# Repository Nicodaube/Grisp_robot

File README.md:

# GRiSP2 Robot

## Introduction

This project is an extension of the master thesis made by Francois Goens and Cédric Ponsard (link [here](https://github.com/FrancoisGgg/balancing_robot) (2023-2024)). It is done in the context of a new master thesis by Nicolas Daube and Thomas Vanbever (2024-2025). Both of these master thesis where done under the supervision of Prof. Peter Van Roy at UCLouvain. The goal of this project is to use [GRISP2 boards](https://github.com/grisp/grisp) (designed and comercialised by [Peer Stritzinger GMBH.](https://stritzinger.com/)) and the [Hera](https://github.com/Nicodaube/hera) framework to create a robot capable of standing upright (last master thesis) and to know its own position in an assembly of rooms (current project). The robot, and its associated sensors, need to know at all time the position of the robot in the system of rooms. Each sensor knows all the data sent by each sensors and by the robot. An other goal of this project is thus to allow each sensor to compute the position of the robot (using a Kalman Filter) at a reasonable rate. This implies that the filter must evolve over time, using the data given by the right sensors at the right time.

The project is done using Erlang OTP (current version 27.2.4). If you want more informations about the, project, visit our the [Wiki](https://github.com/Nicodaube/Grisp_robot/wiki) section of this repository.

## Organisation

This repository is organised in several subdirectories :

* **Hardware_robot** : contains all the necessary files to build the robot. In `Hardware_robot/printing_files` you will find all the files for the prints in 3D and the laser cuts.
* **Hardware_sensor** : Contains all the necessary files to build the sensors and their supports.
* **Laptop_controller** : contains all the code concerning the python server and controller for the robot. Note that its use is mandatory to have a fully functional system.
* **LilyGo_software** : contains all the code for the two LilyGO used in this project. They are used for communication between the robot and the controller.
* **Wiki_image** : just a directory containing all the wiki and README images.
* **balancing_robot** : contains all the code for the auto-stabilized robot.
* **electronics**: contains the files concerning the custom PCB designed for the robot.
* **sensor**: contains all the erlang code for the implementation of the sonar sensors.

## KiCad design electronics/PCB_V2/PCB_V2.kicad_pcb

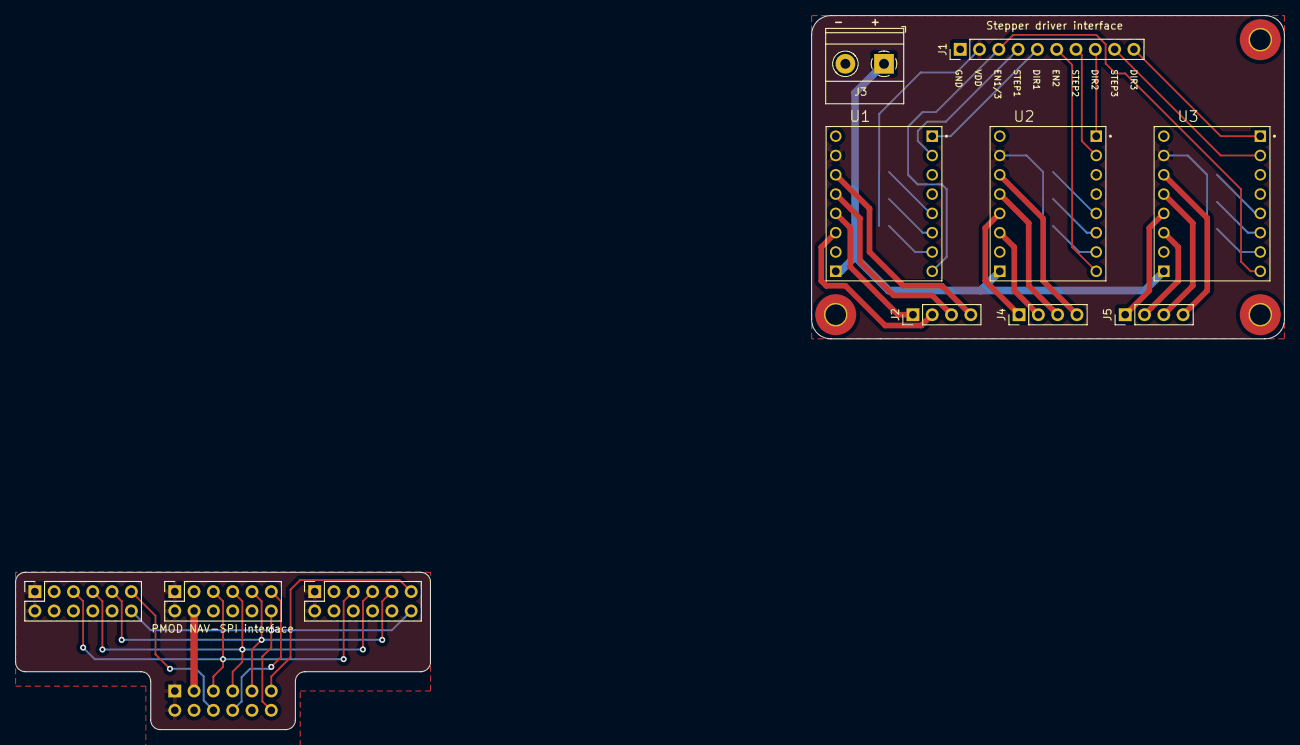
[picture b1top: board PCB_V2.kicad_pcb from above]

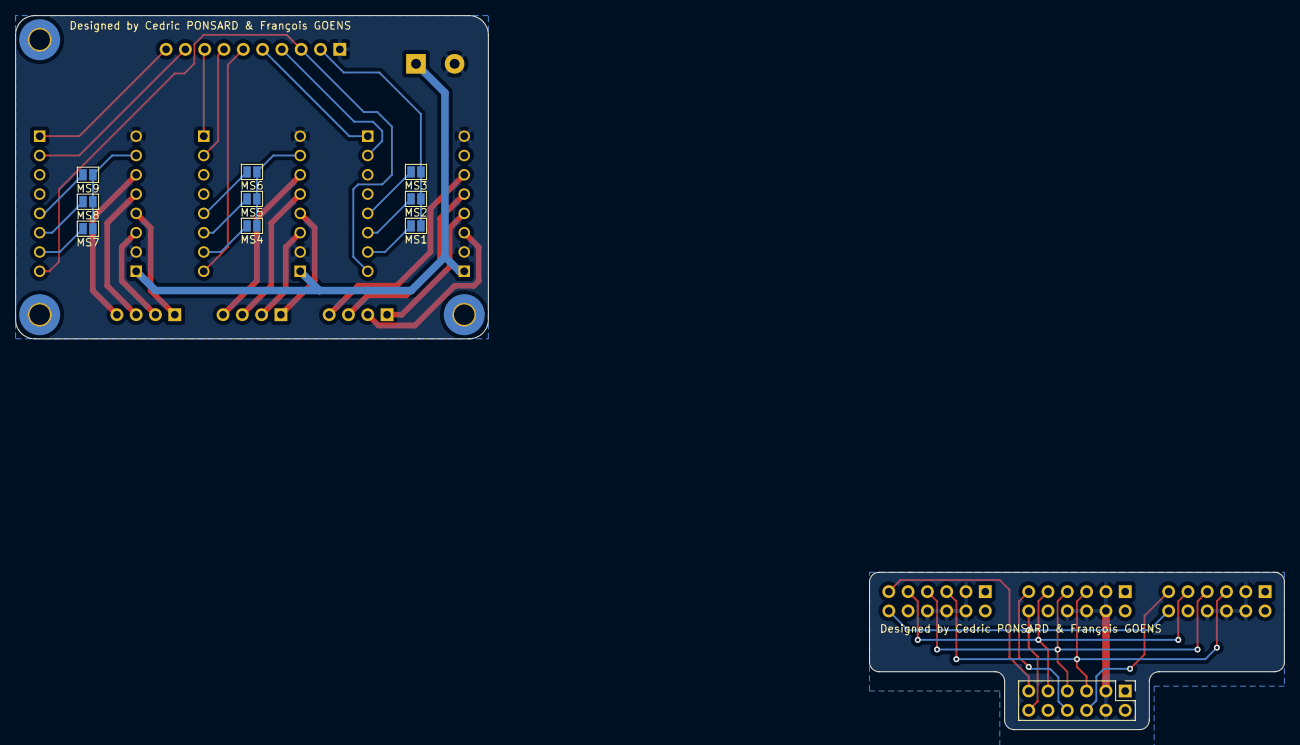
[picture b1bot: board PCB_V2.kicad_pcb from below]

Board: 2 copper layers, 62.2 x 42.5 mm, 21 parts (10 on the bottom side), 39 nets.

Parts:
J1: Conn_01x10_Socket; PinHeader_1x10_P2.54mm_Vertical
J2, J4, J5: Conn_01x04_MountingPin; PinHeader_1x04_P2.54mm_Vertical
J3: Conn_01x02; TerminalBlock_Phoenix_MKDS-1,5-2-5.08_1x02_P5.08mm_Horizont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
J6: Conn_02x06_Odd_Even; PinHeader_2x06_P2.54mm_Vertical
J7, J8, J9: Conn_02x06_Odd_Even; PinSocket_2x06_P2.54mm_Vertical
MS1, MS2, MS3, MS4, MS5, MS6, MS7, MS8, MS9: SolderJumper_2_Open; SolderJumper-2_P1.3mm_Open_Pad1.0x1.5mm
U1, U2, U3: TMC2208_SILENTSTEPSTICK; MODULE_TMC2208_SILENTSTEPSTICK

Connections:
CS1: J6.11, J9.11
CS2: J6.8, J8.11
CS3: J6.6, J7.11
DIR1: J1.5, U1.JP1_1 (DIR)
DIR2: J1.8, U2.JP1_1 (DIR)
DIR3: J1.10, U3.JP1_1 (DIR)
EN1/3: J1.3, U1.JP1_8 (EN), U3.JP1_8 (EN)
EN2: J1.6, U2.JP1_8 (EN)
GND: J1.1, J3.2, J6.3, J6.4, J7.3, J7.4, J7.6, J7.8, J8.3, J8.4, J8.6, J8.8, J9.3, J9.4, J9.6, J9.8, U1.JP2_2 (GND), U1.JP2_8 (GND), U2.JP2_2 (GND), U2.JP2_8 (GND), U3.JP2_2 (GND), U3.JP2_8 (GND)
INT: J6.12, J7.12, J8.12, J9.12
MISO: J6.7, J7.7, J8.7, J9.7
MOSI: J6.9, J7.9, J8.9, J9.9
unnamed: J2.1, U1.JP2_4 (OA1)
unnamed: J2.2, U1.JP2_3 (OA2)
unnamed: J2.3, U1.JP2_5 (OB1)
unnamed: J2.4, U1.JP2_6 (OB2)
unnamed: J3.1, U1.JP2_1 (VM), U2.JP2_1 (VM), U3.JP2_1 (VM)
unnamed: J4.1, U2.JP2_4 (OA1)
unnamed: J4.2, U2.JP2_3 (OA2)
unnamed: J4.3, U2.JP2_5 (OB1)
unnamed: J4.4, U2.JP2_6 (OB2)
unnamed: J5.1, U3.JP2_4 (OA1)
unnamed: J5.2, U3.JP2_3 (OA2)
unnamed: J5.3, U3.JP2_5 (OB1)
unnamed: J5.4, U3.JP2_6 (OB2)
unnamed: MS1.2 (B), U1.JP1_7 (MS1)
unnamed: MS2.2 (B), U1.JP1_6 (MS2)
unnamed: MS3.2 (B), U1.JP1_5 (PDN/UART2)
unnamed: MS4.2 (B), U2.JP1_7 (MS1)
unnamed: MS5.2 (B), U2.JP1_6 (MS2)
unnamed: MS6.2 (B), U2.JP1_5 (PDN/UART2)
unnamed: MS7.2 (B), U3.JP1_7 (MS1)
unnamed: MS8.2 (B), U3.JP1_6 (MS2)
unnamed: MS9.2 (B), U3.JP1_5 (PDN/UART2)
SCK: J6.5, J7.5, J8.5, J9.5
STEP1: J1.4, U1.JP1_2 (STEP)
STEP2: J1.7, U2.JP1_2 (STEP)
STEP3: J1.9, U3.JP1_2 (STEP)
VDD: J1.2, J6.1, J6.2, J7.1, J7.2, J8.1, J8.2, J9.1, J9.2, MS1.1 (A), MS2.1 (A), MS3.1 (A), MS4.1 (A), MS5.1 (A), MS6.1 (A), MS7.1 (A), MS8.1 (A), MS9.1 (A), U1.JP2_7 (VIO), U2.JP2_7 (VIO), U3.JP2_7 (VIO)

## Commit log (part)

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2024-07-24 adding all files and dirs
2024-07-24 update code for compiling
2024-08-01 modifs
2024-08-17 removing prints and unnecessary code
2025-02-18 keep udating readme
2025-02-18 Keep creating README
2025-02-19 Modif rebar.config and Advancement README
2025-02-19 small README
2025-02-23 Start UI refactor
2025-02-24 [REFACTOR] UI
2025-02-24 [REFACTOR] Small ui refactor
2025-02-24 [ADD] Electronics + Hardware add
2025-02-25 [ADD] First room drawing
2025-02-25 [ADD] Plus on each wall
2025-02-25 [REFACTOR] Changed plus identifiers
2025-02-26 [Add] change code
2025-02-26 [FIX] Microsteps + motor side
2025-02-26 Modif_lilygo
2025-03-04 [ADD] Room adder UI
2025-03-04 [MODIF] Changed App Name
2025-03-05 [REFACTOR/ADD] Refactored event handler and start sensor adder
2025-03-07 [REFACTOR] Big refactoring
2025-03-07 [ADD] pluses dissapear
2025-03-07 [ADD] Adding sensors to rooms
2025-03-08 [ADD] Initial sensor commit
2025-03-08 [ADD] PCB and motor engine images
2025-03-08 [ADD] Start wifi tryouts
2025-03-11 [ADD] Sensor connection to WIFI
2025-03-11 [ADD] Sensor sends measurements to Laptop
2025-03-11 [ADD] sensor rounds measurements to mm
2025-03-11 [ADD] Again
2025-03-12 [ADD] Ip to dst msg
2025-03-15 [ADD] Set the sonar frequency to 2Hz
2025-03-15 [ADD] initial server commit
2025-03-15 [ADD] Record the sensors IP
2025-03-15 [ADD] Changed the Sensor IP to just Hello
2025-03-16 [ADD] Id compute
2025-03-17 [FIX] Bug with Id calculation
2025-03-17 [ADD] Connecting server and Controller
2025-03-17 [ADD] preview laser cuts
2025-03-17 [ADD] comments for stability engine code + hera_interface (logging)
2025-03-18 [ADD] RESIZE param, Grid compute + absolute pos (buggy)
2025-03-18 [ADD] max_compatibility.gif
2025-03-18 [ADD] Wifi network image
2025-03-20 [MODIF] end comment main loop
2025-03-20 [MODIF] comments helper module
2025-03-20 [MODIF] reset the rebar.config file
2025-03-20 [MODIF] Reset rebar.config
2025-03-20 [FIX] Reset control to go in the right direction
2025-03-20 [FIX] Correct position computation (still 2/3 cm of error in multi room env)
2025-03-20 [ADD] Send server
2025-03-20 [DELETE] mini_server.py
2025-03-25 [ADD] modif in sensor
2025-03-26 [UPDATE] added folders to gitignore
2025-03-30 [ADD] trajectories to
2025-03-30 [REFACTOR/ADD] Refact trajectory + Add emergency stop
2025-03-31 [ADD] zoom in out for one room
2025-04-01 [ADD] trajectory between doorm rooms
2025-04-01 [MODIF] WIKI add_room and move_ctrl
2025-04-01 [FIX] Fix the two room save bug
2025-04-01 [REFACTOR] Sensors are Object in Server, differenciating uni and broadcast in server
2025-04-01 [MODIF] Sensor position are updated not yet sent
2025-04-01 [ADD] Send position at start
2025-04-05 [FIX] Small bug fix where server crashed when sensor wasn't set in a room
2025-04-06 [ADD] Sensor starts measurements after random time
2025-04-07 [REFACTOR] sensor parse pos
2025-04-07 [MODIFY] Change to accomodate new Hera version
2025-04-07 [ADD] Device message adder
2025-04-08 [ADD] Added Pmod sonar wiki img
2025-04-08 [ADD] Triangle image wiki
2025-04-08 [FIX] CosineLawImg
2025-04-08 [ADD] Bit of commenting in sensor
2025-04-10 main refactor
2025-04-12 [ADD] New General Readme
2025-04-12 [DOC] Repo organisation
2025-04-12 [ADD] Robot angle computation (should work)
2025-04-12 [ADD] Deploy script
2025-04-12 [REFACTOR] Renamed robot_angle to target_angle
2025-04-12 [REMOVE] robot_angle
2025-04-12 [ADD] Sending angle to everybody
2025-04-12 [ADD] Keeps trying to connect to wifi
2025-04-12 [ADD] Wait for Ack before starting loop
2025-04-12 [FIX] target_angle unicast
2025-04-12 [ADD] Sonar send a message before measuring
2025-04-13 [MODIF] Changed timeout
2025-04-14 [ADD] Start and modified measure notif
2025-04-14 [REFACTOR/DOCU] Modified Logs and refactor find room
2025-04-14 [MODIF] Hera notifies connection
2025-04-14 [ADD] Sensor discovers server
2025-04-15 [WIKI] Modif banderole
2025-04-15 [WIKI] Banderole ok
2025-04-16 [DOCU] Sensor documentation
2025-04-17 [FIX] Server Exit (can't restart for now)
2025-04-17 [FIX] Can relaunch computations
2025-04-17 [ADD] Possible to put sensors in corners
2025-04-17 role of grisp
2025-04-17 [REFACTOR] Robot
2025-04-18 [FIX] Kalman number of arguments
2025-04-20 [REWIND] Pre refactor
2025-04-20 [ADD] Drawing robots
2025-04-20 [ADD] sending robot pos to sensors
2025-04-20 [REFACTOR] Renaming get_sensor_pos
2025-04-21 [MODIF] Modified robot creation
2025-04-21 [FIX] Bug with sensor Id
2025-04-21 [MODIF] Can only place robot once
2025-04-21 [MODIF] Changed LEDs meaning
2025-04-21 [ADD] Can define sensor's height
2025-04-21 [FIX] Crash of measure at exit + [ADD] Robot_height Macro
2025-04-21 [FIX] Typo in sensor
2025-04-21 [FIX] Bug with inserting sensors in corners
2025-04-21 [ADD] sensor angle computation
2025-04-22 Create Sensor_build
2025-04-22 [REFACTOR] Target_angle uses her_measure behaviour
2025-04-22 [REFACTOR] Renamed Sensor_build to Hardware Sensor
2025-04-22 [REFACTOR] Moved Sensors 3D files in folder
2025-04-23 [ADD] Created the basic kalman measure module
2025-04-23 [ADD] modified exit and start sequences
2025-04-23 [REFACTOR] Sensor
2025-04-23 [DOCU] commented sensor's code
2025-04-23 [DOCU] Commented the three hera_measure modules
2025-04-23 [ADD] Start Wifi setup robot
2025-04-24 [NOT FUNCTIONAL] Robt refactor
2025-04-24 [FIX] Adapted sensor to new hera version
2025-04-24 [REFACTOR] Whole balancing robot app (not working yet)
2025-04-24 first version of kalman filter
2025-04-24 [ADD] Fonction Tektonik robot (Il convulse mais n'arrive pas à rester debout)
2025-04-27 Second version of kalman filter
2025-04-28 [FIX] Correct Gy0
2025-04-28 [MODIF] Robot at 225H
2025-04-29 [MODIF] A bit more opti
2025-04-29 [RESET] Initial working robot version
2025-04-30 [REFACTOR] step 2 : delete logging, i2C in persistent term
2025-04-30 [REFACTOR] Step 3 : modified state determination
2025-04-30 [REFACTOR] Step 4 : keep refactoring state
2025-04-30 [REFACTOR] Step 5 : deleted complementary filter
2025-04-30 [REFACTOR] Step 7 : Grouped kalman Operations
2025-04-30 [REFACTOR] Step 8 : state + Deleted useless Comments
2025-04-30 [OPTI] Removed kalman constant
2025-04-30 [REFACTOR] Step 9 : Removed Pid from arguments
2025-04-30 [REFACTOR] Changed Arguments to a map
2025-04-30 [REFACTOR] Step 12 : Replaced Wait by sleep and modified comments
2025-04-30 [REFACTOR] Step 13 : Code reorganisation
2025-04-30 [REFACTOR] Step 14: Last small things
2025-05-01 [ADD] Wifi connection
2025-05-01 [ADD] Server adaptation
2025-05-01 [ADD] Set Up main receiver loop
2025-05-01 [ADD] Kalman_measure
2025-05-03 [ADD] Update robot pos based on robot message
2025-05-12 [FIX] small error in LEDS colors
2025-05-14 [MODIF] Update main README
2025-05-18 [WIKI] Sensor FSM
2025-05-19 [FIX] Robot pos update
2025-05-19 [FIX] Dist between sensors was in meters
2025-05-20 [MODIF] Upgraded sync between sensors
2025-05-20 [MODIF] No Click to spawn robot, popup instead (not working yet)
2025-05-20 [MODIF] Form works + Renamed RC_ROBOT -> Controller
2025-05-20 [MODIF] Moved other sensor finding in sensor
2025-05-20 [ADD] Sending master to Osensor
2025-05-21 [FIX] Fixed the synchronization problem
2025-05-21 [FIX] Bloqued in handshake when crashed
2025-05-21 [FIX] Sonar Sensor restarts from latest Seq number when crash
2025-05-22 [FIX] Target angle works for sensor slightly up from the ground
2025-05-22 [FIX] Fixed bug that tried to get distance when relaunching after exit
2025-05-22 [FIX] No duplication of messages when restarting
2025-05-22 [FIX] No dup when restart robot
2025-05-22 [DOCU] Corrected robot comments
2025-05-23 [ADD] Basic acknowledgement works
2025-05-23 [FIX] Allow mono sensor in room
2025-05-23 [ADD] Start of robot ack
2025-05-24 [ADD] Add Apache License
2025-05-24 [MODIF] Updated balancing robot License
2025-05-24 [ADD] Added Apache License
2025-05-24 [MODIF] Update LICENSE
2025-05-24 [ADD] Robot and sensor succesfully ack their config messages
2025-05-24 [ADD] Added a script to run multiple times the Controller
2025-05-24 [DOCU] Resseted the documentation to match the ones of the sensors
2025-05-26 [DOCU] Modified incorrect SENSOR indentificator to ROBOT
2025-05-26 [REFACTOR] Server refactored and Controller files packaged
2025-05-26 [DOCU] Generalized doc
2025-05-26 [FIX] Reactivated serial comm
2025-05-28 [ADD] BUGGY Try to get the robot pos by sonars
2025-05-28 [FIX] Removed server print when exception
2025-05-28 [ADD] csv_saver
2025-06-02 [WIKI] Add sensor img
2025-06-02 [MODIF] Auto user determination deploy script
2025-06-02 [ADD] Computes Ground dist only if H > Robot height
2025-06-02 [MODIF] Added timestamp to csv saver
2025-06-03 [ADD] Formatted messages and implemented csv_saver dist and fq
2025-06-03 [ADD] Better fq, better sync
2025-06-04 [FIX] Beginning fix kalman sensor
2025-06-04 [REFACTOR/DOCU] kalman_measure
2025-06-04 [ADD] Gather nav data
2025-06-06 [ADD] New lilygo access point
2025-06-10 [ADD] Buggy switch network
2025-06-10 [FIX] Good position using sonars, still need to select the correct one using room coordinates
2025-06-10 [ADD] Sensors and robot receive rooms limits
2025-06-10 [ADD] Bis
2025-06-10 [ADD] Delete the false (x,y) position
2025-06-10 [Kalman Filter] First version with nav and pos
2025-06-10 [Kalman Filter] Just position without Acc
2025-06-10 [kalman filter] XY with Acc, Test
2025-06-11 [FIX] Casted room positions to float
2025-06-11 [ADD] Working kalman, not very precise (x,y)
2025-06-11 [ADD] graph_creator
2025-06-11 [FIX] No negative value kalman
2025-06-11 [FIX] Correct sonar_sensor + room_infos
2025-06-11 [ADD] Sensors use 300ms timeslots
2025-06-11 [MODIF] Gitignores
2025-06-11 [MODIF] Removed caches
2025-06-12 [ADD/FIX] Sonar sensor filters out spikes + corrected csv_saver plot
2025-06-12 [kalman filter] UpDate when no intersection
2025-06-12 [kalman filter] UpDate when no interaction
2025-06-12 [ADD] Plot pos
2025-06-12 [ADD] Accept range = 15 + store data at least once each timeslot
2025-06-13 [FIX] Corrected Kalman logic
2025-06-13 [FIX] Controller plot printing
2025-06-13 [MODIF] Better computation rate
2025-06-13 [MODIF] Save data using timestamp not idx
2025-06-14 [kalman filter] Full liaison position angle
2025-06-14 [FIX] Min measure works
2025-06-14 [MODIF] End Kalman Pos
2025-06-14 [FIX] start debuging
2025-06-14 [FIX] numerl in kalman_measure
2025-06-14 [FIX] Fixed lots of types error kalman ok
2025-06-14 [ADD] Robot angle drawn
2025-06-17 [NEW] ekf filter for no linear system
2025-06-17 [FIX] Correct handling of pos data
2025-06-20 [ADD] Exponential smoothing sonars
2025-06-21 [ADD] SPI slave monitor messages
2025-06-21 [ADD] Better Run script
2025-06-22 [kalman filter] Avant gros changement simplification
2025-06-22 [MODIF] I don't knwow what to do
2025-06-22 [FIX] Multi start robustness
2025-07-01 [ADD] The lilygoBot now is a Wifi AP
2025-07-01 [DEL] Removed lily access point
2025-07-02 [ADD] Clock seems right
2025-07-02 [Kalman upgrade] new one
2025-07-03 [MODIF] Increased Maximum number of WiFi connection (Attention to througput)
2025-07-03 [Last change] Check var kalman
2025-07-04 [TESTE] PAs concluant
2025-07-05 [Kalman] Without Xpred when no sonar
2025-07-05 [Kalman Update] Acceleration update ??
2025-07-05 [Kalman Update] Better
2025-07-06 [MODIF] Upgraded and simplified clock and sonar_sensors
2025-07-06 [MODIF] gitignore
2025-07-06 [ADD] Exit modules
2025-07-07 [MODIF] Working filter sonar
2025-07-07 [MODIF] Best parameters yet
2025-07-08 [FIX] Corrected sonar pos
2025-07-11 [New kalman] normal kalman
2025-07-11 [FIX] Fixed small clock errors
2025-07-11 [FIX] Non exiting robot
2025-07-11 [ADD] Sys.config sensor
2025-07-11 [MODIF] Relaxed sonar filters
2025-07-11 [FIX] Kalman verif seq sonar
2025-07-11 [MODIF] New version
2025-07-14 [ADD] Room change logic
2025-07-17 [Kalman] fixe Z for transfere piece
2025-07-17 [ADD] determine room kalman
2025-07-17 [Switch room] Add switch room in kalman
2025-07-17 [Check angle] Trucs chelou
2025-07-29 [ADD/REFACTOR] Switch room done
2025-08-04 [Kalman Filter] Final version
2025-08-04 [ADD] Gossip protocol
2025-08-07 [ADD] Gossip works but congestion
2025-08-08 [ADD] Propagation ok
2025-08-08 [FIX] Reset rebar and sys config to main
2025-08-10 [Kalman update]
